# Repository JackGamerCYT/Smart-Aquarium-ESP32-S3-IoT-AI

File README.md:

# Smart Aquarium v5.0: sò lạnh PID + bơm nước bật/tắt riêng

Module sưởi USB 5W tự giữ nước ở khoảng 26 °C, nên ESP32 **không điều khiển sưởi** nữa. ESP32 chỉ còn làm hai việc bằng 2 MOSFET IRLZ44N: điều khiển **sò lạnh Peltier 12V** bằng PID một phía (chỉ làm lạnh), và **bật/tắt động cơ bơm nước** riêng. Ngoài ra vẫn có cho cá ăn bằng servo, màn OLED, và giám sát/điều khiển từ xa qua MQTT, backend Render + Postgres Neon, dashboard trên Vercel.

> Môn Embedded System Design (GVHD Huỳnh Hoàng Hà, HCMUTE). Linh kiện đúng theo sơ đồ `hehehehe.pdsprj`, **không thêm linh kiện nào**.

```text
smart_aquarium_v5/
├── firmware/
│   ├── smart_aquarium_cool/    firmware chính v5 (sò PID + bơm + MQTT + OLED + cho ăn)
│   ├── test_bom_so/            test Q1 (bơm) và Q2 (sò): bật 3s, tắt 3s; lệnh 1/2/0/a
│   ├── test_ds18b20/           test cảm biến ở GPIO6 (cổng SERVO 2)
│   ├── test_oled/              test OLED 0x3C
│   └── test_servo/             test servo cho ăn ở GPIO7
├── backend/                    Node: nghe MQTT, ghi Postgres, REST API, trợ lý dữ liệu
│   └── device_sim.js           mô phỏng ESP32 v5 (có cả thermostat của module sưởi)
├── index.html                  Web dashboard v7 (deploy lên Vercel)
├── render.yaml · vercel.json · .env.example
```

---

## 1. Nối chân (theo PCB)

| Chân ESP32-S3 | Trên mạch | Nối với |
|---|---|---|
| GPIO4 (IN1) | R1 2K2 → Gate Q1, **kênh C1** | **Động cơ bơm nước** (bật/tắt, khởi động mềm ~1 s) |
| GPIO5 (IN2) | R2 2K2 → Gate Q2, **kênh C2** | **Sò lạnh Peltier 12V** (PWM 200 Hz) |
| GPIO6 | cổng SERVO 2 | **DS18B20**: chân 3 DATA, chân 2 VCC (3V3), chân 1 GND |
| GPIO7 | cổng SERVO 1 | Servo MG90S cho ăn |
| GPIO8 / GPIO9 | U2, TGT | OLED 0.96" 0x3C (SDA / SCL) |
| GPIO0 | nút BOOT trên DevKit | Bấm để cho ăn ngay |
| — | ngõ ra 5V của LM2596 | **Module sưởi USB 5W** (tự giữ ~26 °C, ESP32 không điều khiển) |

**Kiểm tra đúng kênh trước khi chạy firmware chính:** nạp `test_bom_so`, mở Serial 115200, gõ `1`. Phải là **bơm** chạy. Nếu sò chạy thì trong `smart_aquarium_cool.ino` đổi `PIN_PUMP` thành 5 và `PIN_COOL` thành 4.

### ⚠️ Đi dây cho v5

1. **Sò lạnh nằm ở kênh C2 (Q2).** Kênh này trước đây nối tải 5V. Dây (+) của sò phải nối vào **12V**, không phải 5V. Sò kéo khoảng 5 A: hàn dây to thẳng vào chân D của Q2, và **gắn tản nhiệt cho Q2** (IRLZ44N tỏa khoảng 1,5 W khi gate chỉ được kích 3,3V).
2. **Bơm nằm ở kênh C1 (Q1).** Dây (+) của bơm nối vào nguồn đúng điện áp của bơm (5V hay 12V). Cực (−) vào lỗ phía chân D của Q1.
3. **Module sưởi USB** lấy 5V từ ngõ ra LM2596, chung với ESP32 và servo. 5 W ở 5V là khoảng 1 A, cộng ESP32 và servo vẫn dưới mức 3 A của LM2596.
4. Các sửa lỗi của bản trước vẫn áp dụng:
   - Tháo R3/R4 nối tiếp ở chân D, chập domino để chân S xuống thẳng GND.
   - Servo lấy 5V (không lấy 3V3).
   - OLED lấy 3V3 nếu SDA/SCL đo ra 5V.
5. Sò **bắt buộc** có tản nhiệt và quạt ở mặt nóng. Quạt cắm thẳng 12V, chạy liên tục.

---

## 2. Thuật toán điều khiển

```
e = Nhiệt độ đặt − Nhiệt độ đo              (e < 0: nước nóng hơn mức đặt)
u = Kp·e + Ki·∫e dt − Kd·dT/dt   ∈ [−cool_max … 0] %
u < −3%  → sò lạnh PWM = |u|
```
- **Chỉ làm lạnh.** Tích phân bị kẹp trong [−cool_max, 0]. Khi nước lạnh hơn mức đặt (lúc sưởi USB đang làm ấm), tích phân chỉ xả về 0, không tích dương. Vì vậy khi nước nóng lên lại, sò phản ứng ngay.
- **Không "đánh nhau" với sưởi.** Nhiệt độ đặt tối thiểu = nhiệt sưởi USB + 0,5 °C (mặc định 26 + 0,5 = **26,5 °C**, nhiệt đặt mặc định **27 °C**).
  - Nhiệt sưởi USB chỉnh được trên web cho khớp với module thật.
  - Nếu tăng nhiệt sưởi làm mức đặt hiện tại thấp hơn giới hạn, firmware tự nâng mức đặt lên.
- **Vùng chết, chống vọt lố, khâu D theo nhiệt độ đo, tăng công suất tối đa 20%/s:** giữ như v4.
- **Bơm:** BẬT/TẮT riêng, trạng thái được lưu vào bộ nhớ (mất điện bật lại vẫn giữ). Khởi động mềm 0 → 100% trong khoảng 1 s để giảm dòng khởi động.
- **Khóa sò theo bơm** (`cool_need_pump`, mặc định BẬT): tắt bơm thì sò tạm khóa. Nên giữ BẬT nếu sò làm lạnh qua đường nước mà bơm đẩy; tắt đi nếu tấm lạnh của sò ngâm thẳng trong bể.

| Tình huống | Firmware xử lý |
|---|---|
| Sò ở chế độ OFF | Sò tắt hẳn, kể cả khi nước ≥ 31 °C. Bơm không bị ảnh hưởng |
| Mất cảm biến (3 lần đọc lỗi hoặc 5 s không có số mới) | Tắt sò. Bơm vẫn chạy |
| Bơm tắt và đang bật khóa sò theo bơm | Tắt sò (`cool_block = PUMP_OFF`) |
| Nước ≥ 31 °C (AUTO/MANUAL) | Sò chạy tối đa, báo `TEMP_HIGH` |
| Nước ≤ 20 °C | Tắt sò, báo `TEMP_LOW` (module sưởi USB có thể hỏng) |
| AUTO, nước < nhiệt đặt − 1,5 °C | Không làm lạnh |

- **Chế độ sò:** AUTO (PID) · MANUAL (đặt % tay, tự về AUTO sau 30 phút) · OFF.
- **Tham số mặc định:** Kp = 60, Ki = 0,01, Kd = 0, vùng chết 0,1 °C, sò tối đa 100%.

### Chỉnh PID (mục "Tham số PID" trên web)
1. Đặt Ki = 0, Kd = 0. Tăng Kp đến khi nhiệt độ dao động nhẹ quanh điểm đặt, rồi giảm Kp còn khoảng 60%.
2. Tăng Ki từ 0,005 để xóa sai lệch còn lại. Nếu vọt lố nhiều thì giảm Ki.
3. Kd thường để 0.
4. So sánh các bộ tham số bằng ô "Sai số bám (AUTO)" và "% thời gian trong ±0,5 °C".

---

## 3. Nạp firmware

1. Arduino IDE → Boards Manager → **esp32 by Espressif** (bản 3.x hoặc 2.x) → board **ESP32S3 Dev Module**.
2. Library Manager → cài **PubSubClient** (Nick O'Leary) và **ArduinoJson** (bản 7).
3. Chạy `test_bom_so` trước để xác nhận kênh bơm/sò (mục 1).
4. Mở `firmware/smart_aquarium_cool/smart_aquarium_cool.ino`, sửa `WIFI_SSID`, `WIFI_PASS`, `TOPIC_BASE` rồi nạp.

**Lệnh qua Serial Monitor (115200):**

| Lệnh | Tác dụng |
|---|---|
| `status` | In trạng thái |
| `auto` · `manual` · `off` | Đổi chế độ sò lạnh |
| `sp 27` | Đặt nhiệt độ làm lạnh (≥ nhiệt sưởi + 0,5) |
| `cool 50` | Chạy tay sò 50% (MANUAL 30 phút) |
| `pump on` · `pump off` | Bật / tắt bơm |
| `hsp 26` | Khai báo nhiệt sưởi USB |
| `needpump 1` · `needpump 0` | Bật / tắt khóa sò theo bơm |
| `kp 60` · `ki 0.01` · `kd 0` · `db 0.1` | Chỉnh PID |
| `feed` · `sched 07:00,17:30` · `pidreset` · `ds` · `oled …` | Như bản trước |

Màn OLED dòng 5 hiển thị `So xx%  Bom BAT/TAT`.

---

## 4. Backend (Render + Neon) và web (Vercel)

1. **Neon:** tạo database, lấy chuỗi *Pooled connection* (có `?sslmode=require`).
2. **Render:** New → Blueprint → chọn repo (dùng file `render.yaml`) → nhập `DATABASE_URL`. Bảng được tạo tự động. Database cũ (bản relay / v4 PID) dùng tiếp được: backend chỉ **thêm cột `pump` và thông số `pump_w`**, không xóa dữ liệu cũ.
3. **Vercel:** deploy thư mục gốc (web tĩnh `index.html`). Sửa `DEFAULT_API` trong `index.html` thành URL Render của nhóm, hoặc nhập URL ở mục Cài đặt trên web.
4. `TOPIC_BASE` phải trùng nhau ở cả 3 nơi: firmware, biến `MQTT_TOPIC_BASE` trên Render, và `TOPIC_DEFAULT` trong web.

**Test không cần phần cứng:** chạy `cd backend && npm install && node device_sim.js`. Chương trình giả lập ESP32 với đúng giao thức MQTT, kèm mô hình nhiệt của bể và bộ PID giống firmware.

### Giao thức MQTT (`<TOPIC_BASE>/…`)

| Topic | Hướng | Nội dung |
|---|---|---|
| `telemetry` | ESP32 → | Mỗi 2 s: `temp, sp, mode, cool, pump, pump_pct, cool_block, heater_sp, sp_min, sp_max, cool_need_pump, pid_u/p/i/d, kp, ki, kd, db, cool_max, feed_*, alarm, rssi, seq, ts, buf_count, safe_mode…` |
| `command` | → ESP32 | `{"device": …}`, xem bảng dưới |
| `ack` | ESP32 → | `{id, device, ok, msg}` |
| `event` | ESP32 → | `feed, alarm, recovered, mode, setpoint, pid, pump, schedule, time_sync, boot…` |
| `status` | ESP32 → | `online` / `offline` (retain, LWT) |

| `device` | Tham số | Tác dụng |
|---|---|---|
| `mode` | `action`: AUTO / MANUAL / OFF | Chế độ sò lạnh |
| `setpoint` | `value` (nhiệt sưởi + 0,5 … 32) | Nhiệt độ làm lạnh |
| `pid` | `kp, ki, kd, db, cool_max, heater_sp (18–30), cool_need_pump` | Tham số |
| `pid_reset` | – | Xóa tích phân |
| `cool` | `value` (0–100) | Chạy tay sò, MANUAL 30 phút |
| `pump` | `action`: ON / OFF / TOGGLE | Bật / tắt bơm |
| `feed`, `schedule`, `time`, `oled`, `ping` | như bản trước | |

### REST API (backend)

Các endpoint giữ như bản trước. Những chỗ thay đổi:
- `/api/history` trả `cool` và `pump` (% thời gian bơm bật).
- `/api/stats` trả `pump_on_pct`, `pump_runtime_min`, `pump_wh`, `events.pump_switches`.
- `/api/settings` dùng các khóa `cool_w`, `pump_w`, `tariff_vnd_per_kwh`.
- Điện năng không tính module sưởi USB, vì nó tự bật/tắt và ESP32 không biết lúc nào nó chạy.

---

## 5. Đã kiểm tra (v5)

- **Biên dịch:** firmware chính và `test_bom_so` biên dịch với ESP32 core 3.0.7, board ESP32-S3: 0 lỗi, 0 cảnh báo. Firmware chính chiếm 75% flash và 14% RAM.
- **Nâng cấp database:** chạy backend v5 trên database đang có dữ liệu v4. Bảng cũ giữ nguyên, cột `pump` và thông số `pump_w` được thêm tự động.
- **Chạy thật backend + Postgres + Mosquitto + bộ giả lập v5:**
  - Mọi lệnh đều có ACK, độ trễ khoảng 20–45 ms.
  - Tắt bơm thì sò bị khóa (`PUMP_OFF`).
  - Các lệnh sai bị từ chối: nhiệt đặt 26 °C khi sưởi 26 °C, `heater_sp = 35`, `pump MAYBE`, `heat`.
  - Tăng nhiệt sưởi thì mức đặt tự được nâng lên.
- **Kiểm tra web tự động bằng Chromium:**
  - Nút bơm, nút sò, đặt nhiệt, chạy tay, lưu tham số, thống kê, lịch sử và trợ lý đều hoạt động.
  - Không có lỗi JavaScript; giao diện điện thoại không bị tràn ngang.
- **Chưa chạy trên board thật.**

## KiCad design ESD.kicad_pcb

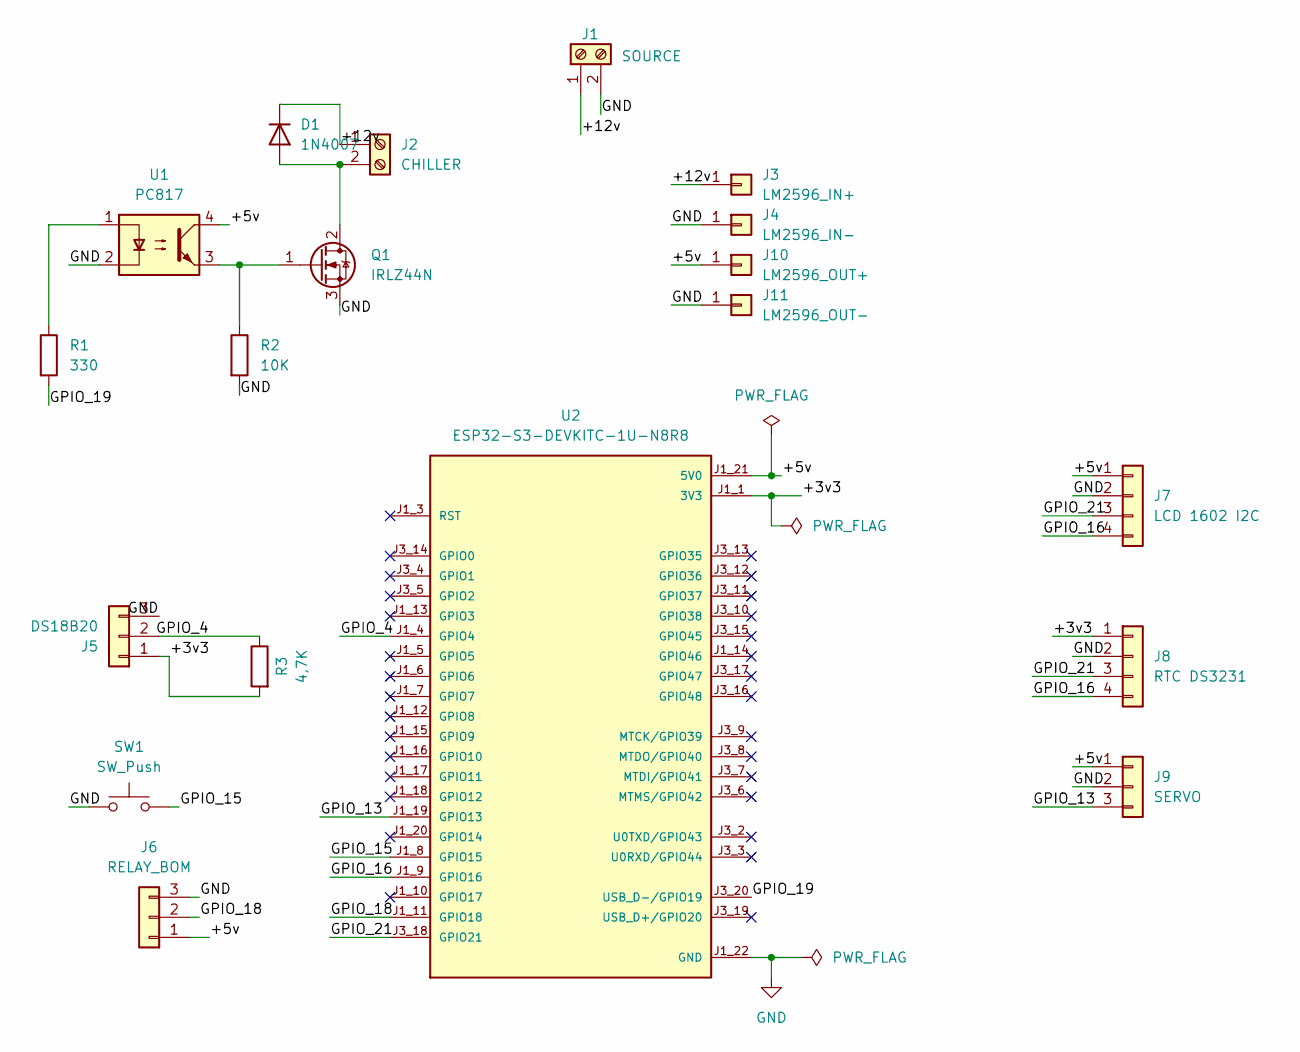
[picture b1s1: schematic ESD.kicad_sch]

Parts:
D1: 1N4007; D_DO-41_SOD81_P10.16mm_Horizontal
J1: SOURCE; TerminalBlock_Phoenix_MKDS-1,5-2-5.08_1x02_P5.08mm_Horizont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
J2: CHILLER; TerminalBlock_Phoenix_MKDS-1,5-2-5.08_1x02_P5.08mm_Horizont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
J3: LM2596_IN+; PinSocket_1x01_P2.54mm_Vertical
J4: LM2596_IN-; PinSocket_1x01_P2.54mm_Vertical
J5: DS18B20; PinHeader_1x03_P2.54mm_Vertical
J6: RELAY_BOM; PinHeader_1x03_P2.54mm_Vertical
J7: LCD 1602 I2C; PinHeader_1x04_P2.54mm_Vertical
J8: RTC DS3231; PinHeader_1x04_P2.54mm_Vertical
J9: SERVO; PinHeader_1x03_P2.54mm_Vertical
J10: LM2596_OUT+; PinSocket_1x01_P2.54mm_Vertical
J11: LM2596_OUT-; PinSocket_1x01_P2.54mm_Vertical
Q1: IRLZ44N; TO-220-3_Vertical
R1: 330; R_Axial_DIN0207_L6.3mm_D2.5mm_P10.16mm_Horizontal
R2: 10K; R_Axial_DIN0207_L6.3mm_D2.5mm_P10.16mm_Horizontal
R3: 4,7K; R_Axial_DIN0207_L6.3mm_D2.5mm_P10.16mm_Horizontal
SW1: SW_Push; SW_PUSH_6mm
U1: PC817; DIP-4_W7.62mm
U2: ESP32-S3-DEVKITC-1U-N8R8; MODULE_ESP32-S3-DEVKITC-1U-N8R8; PARTREV 1.1

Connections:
3V3: J5.1, J8.1, R3.2, U2.J1_1 (3V3), U2.J1_2 (3V3)
/+5v: J6.1, J7.1, J9.1, J10.1, U1.4, U2.J1_21 (5V0)
/+12v: D1.1 (K), J1.1, J2.1, J3.1
/GPIO_4: J5.2, R3.1, U2.J1_4 (GPIO4)
/GPIO_13: J9.3, U2.J1_19 (GPIO13)
/GPIO_15: SW1.2, U2.J1_8 (GPIO15)
/GPIO_16: J7.4, J8.4, U2.J1_9 (GPIO16)
/GPIO_18: J6.2, U2.J1_11 (GPIO18)
/GPIO_19: R1.2, U2.J3_20 (USB_D-/GPIO19)
/GPIO_21: J7.3, J8.3, U2.J3_18 (GPIO21)
GND: J1.2, J4.1, J5.3, J6.3, J7.2, J8.2, J9.2, J11.1, Q1.3 (S), R2.2, SW1.1, U1.2, U2.J1_22 (GND), U2.J3_1 (GND), U2.J3_21 (GND), U2.J3_22 (GND)
unnamed: D1.2 (A), J2.2, Q1.2 (D)
unnamed: Q1.1 (G), R2.1, U1.3
unnamed: R1.1, U1.1

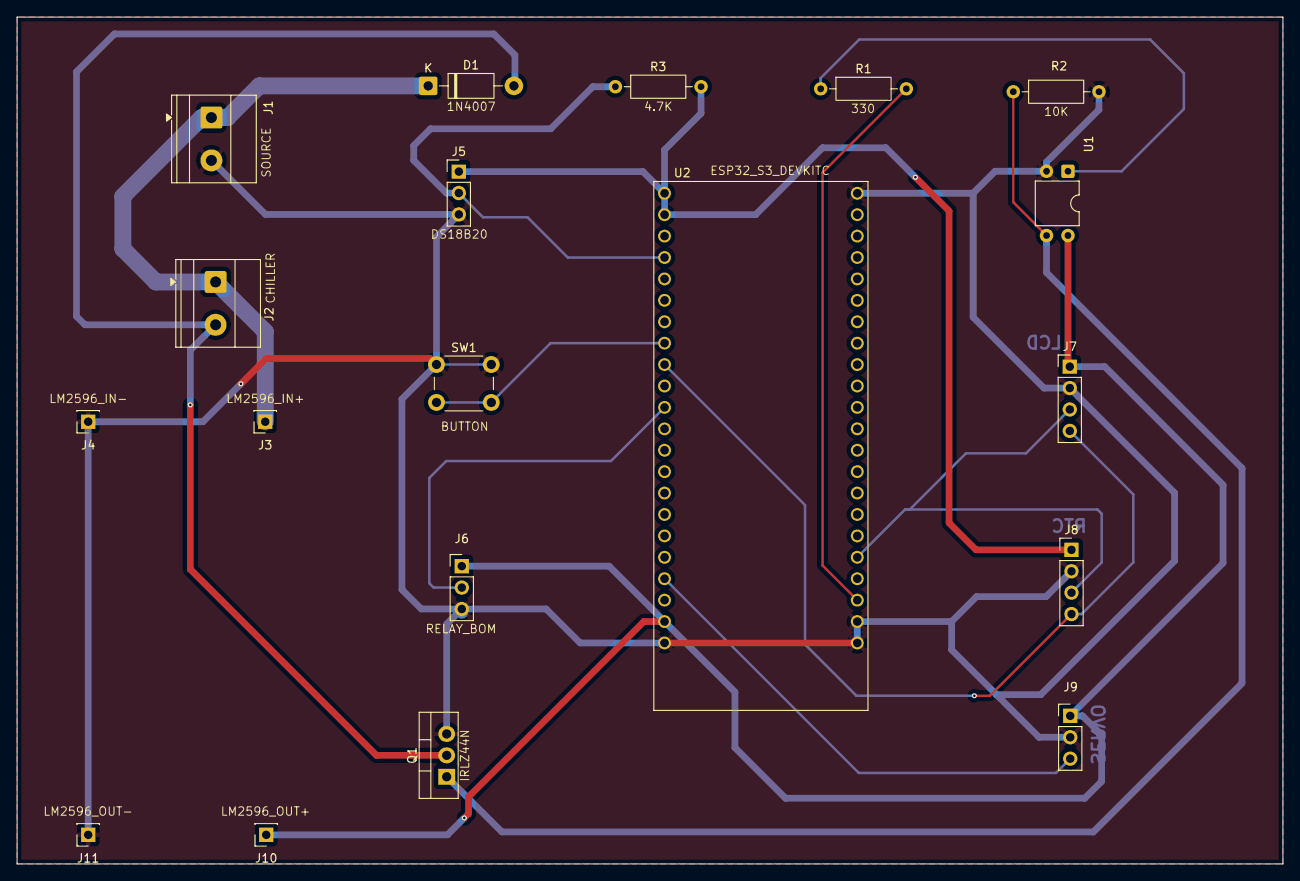
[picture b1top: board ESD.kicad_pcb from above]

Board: 2 copper layers, 150.1 x 100.4 mm, 19 parts (0 on the bottom side), 14 nets.
